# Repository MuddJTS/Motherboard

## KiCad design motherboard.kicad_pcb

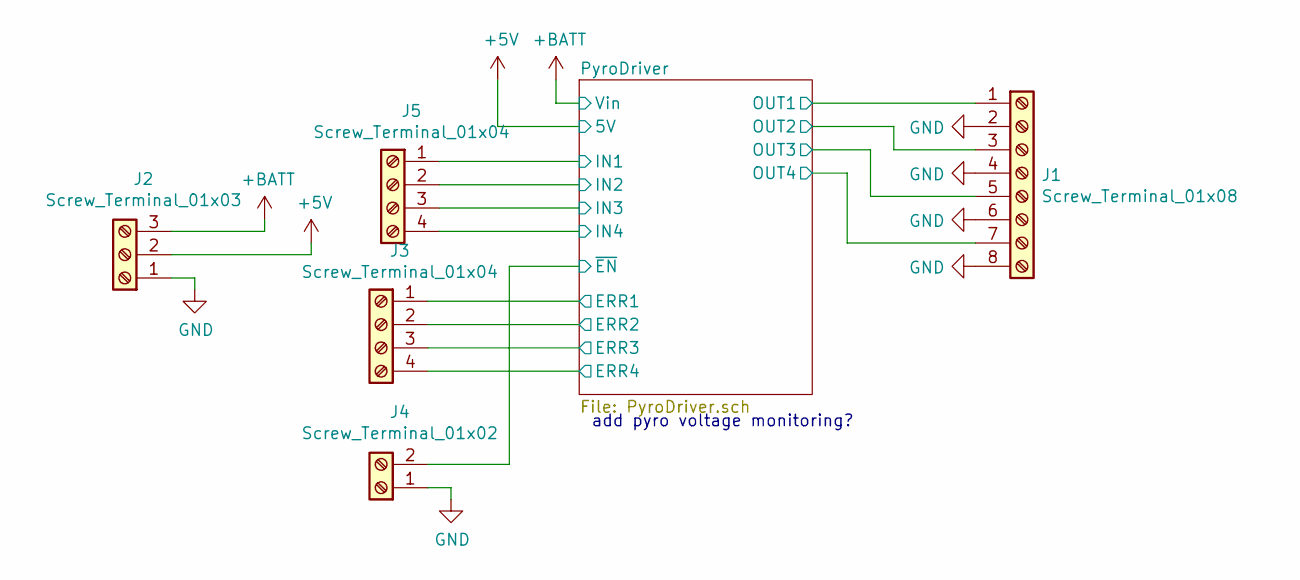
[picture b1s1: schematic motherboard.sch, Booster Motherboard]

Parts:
J1: Screw_Terminal_01x08; IDC-Header_2x04_Pitch2.54mm_Straight
J2: Screw_Terminal_01x03; TerminalBlock_bornier-3_P5.08mm
J3, J5: Screw_Terminal_01x04; TerminalBlock_bornier-4_P5.08mm
J4: Screw_Terminal_01x02; TerminalBlock_bornier-2_P5.08mm

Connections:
+5V: J2.2; also elsewhere on the board
+BATT: J2.3; also elsewhere on the board
/PyroDriver/ERR1: J3.1; also elsewhere on the board
/PyroDriver/ERR2: J3.2; also elsewhere on the board
/PyroDriver/ERR3: J3.3; also elsewhere on the board
/PyroDriver/ERR4: J3.4; also elsewhere on the board
/PyroDriver/IN1: J5.1; also elsewhere on the board
/PyroDriver/IN2: J5.2; also elsewhere on the board
/PyroDriver/IN3: J5.3; also elsewhere on the board
/PyroDriver/IN4: J5.4; also elsewhere on the board
/PyroDriver/OUT1: J1.1; also elsewhere on the board
/PyroDriver/OUT2: J1.3; also elsewhere on the board
/PyroDriver/OUT3: J1.5; also elsewhere on the board
/PyroDriver/OUT4: J1.7; also elsewhere on the board
/PyroDriver/~EN: J4.2; also elsewhere on the board
GND: J1.2, J1.4, J1.6, J1.8, J2.1, J4.1; also elsewhere on the board

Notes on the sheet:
add pyro voltage monitoring?

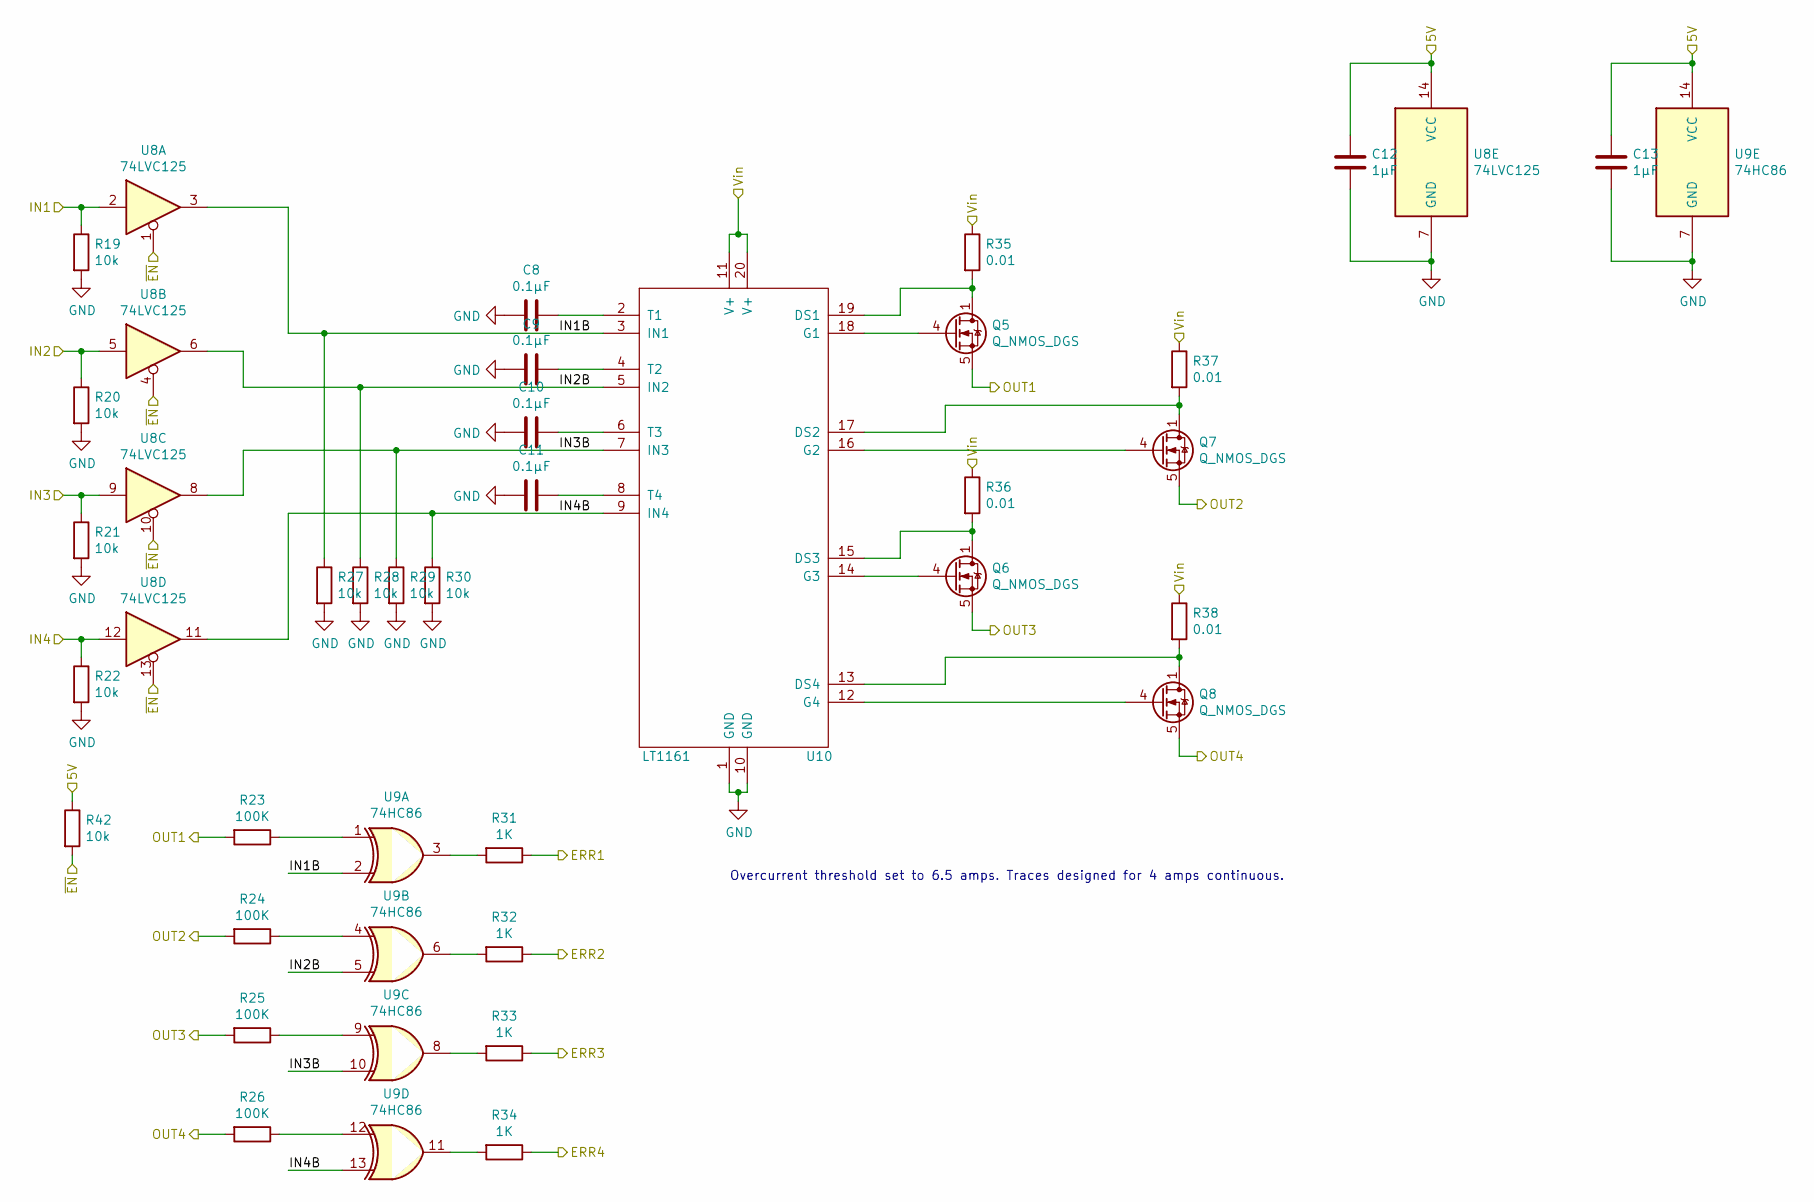
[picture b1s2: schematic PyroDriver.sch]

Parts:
C8, C9, C10, C11: 0.1µF; C_0603_1608Metric
C12, C13: 1µF; C_0603_1608Metric
Q5, Q6, Q7, Q8: Q_NMOS_DGS; PowerPAK_SO-8_Single
R19, R20, R21, R22, R27, R28, R29, R30, R42: 10k; R_0603_1608Metric
R23, R24, R25, R26: 100K; R_0603_1608Metric
R31, R32, R33, R34: 1K; R_0603_1608Metric
R35, R36, R37, R38: 0.01; R_0805_2012Metric
U8: 74LVC125; SOIC-14_3.9x8.7mm_Pitch1.27mm
U9: 74HC86; SOIC-14_3.9x8.7mm_Pitch1.27mm
U10: LT1161; Infineon_PG-DSO-20-32

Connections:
+5V: C12.1, C13.1, R42.1, U8.14 (VCC), U9.14 (VCC); also elsewhere on the board
+BATT: R35.1, R36.1, R37.1, R38.1, U10.11 (V+), U10.20 (V+); also elsewhere on the board
/PyroDriver/ERR1: R31.1; also elsewhere on the board
/PyroDriver/ERR2: R32.1; also elsewhere on the board
/PyroDriver/ERR3: R33.1; also elsewhere on the board
/PyroDriver/ERR4: R34.1; also elsewhere on the board
/PyroDriver/IN1: R19.1, U8.2; also elsewhere on the board
/PyroDriver/IN1B: R27.1, U8.3, U9.2, U10.3 (IN1)
/PyroDriver/IN2: R20.1, U8.5; also elsewhere on the board
/PyroDriver/IN2B: R28.1, U8.6, U9.5, U10.5 (IN2)
/PyroDriver/IN3: R21.1, U8.9; also elsewhere on the board
/PyroDriver/IN3B: R29.1, U8.8, U9.10, U10.7 (IN3)
/PyroDriver/IN4: R22.1, U8.12; also elsewhere on the board
/PyroDriver/IN4B: R30.1, U8.11, U9.13, U10.9 (IN4)
/PyroDriver/OUT1: Q5.5 (S), R23.2; also elsewhere on the board
/PyroDriver/OUT2: Q7.5 (S), R24.2; also elsewhere on the board
/PyroDriver/OUT3: Q6.5 (S), R25.2; also elsewhere on the board
/PyroDriver/OUT4: Q8.5 (S), R26.2; also elsewhere on the board
/PyroDriver/~EN: R42.2, U8.1, U8.4, U8.10, U8.13; also elsewhere on the board
GND: C8.2, C9.2, C10.2, C11.2, C12.2, C13.2, R19.2, R20.2, R21.2, R22.2, R27.2, R28.2, R29.2, R30.2, U8.7 (GND), U9.7 (GND), U10.1 (GND), U10.10 (GND); also elsewhere on the board
unnamed: C8.1, U10.2 (T1)
unnamed: C9.1, U10.4 (T2)
unnamed: C10.1, U10.6 (T3)
unnamed: C11.1, U10.8 (T4)
unnamed: Q5.1 (D), Q5.2, Q5.3, R35.2, U10.19 (DS1)
unnamed: Q5.4 (G), U10.18 (G1)
unnamed: Q6.1 (D), Q6.2, Q6.3, R36.2, U10.15 (DS3)
unnamed: Q6.4 (G), U10.14 (G3)
unnamed: Q7.1 (D), Q7.2, Q7.3, R37.2, U10.17 (DS2)
unnamed: Q7.4 (G), U10.16 (G2)
unnamed: Q8.1 (D), Q8.2, Q8.3, R38.2, U10.13 (DS4)
unnamed: Q8.4 (G), U10.12 (G4)
unnamed: R23.1, U9.1
unnamed: R24.1, U9.4
unnamed: R25.1, U9.9
unnamed: R26.1, U9.12
unnamed: R31.2, U9.3
unnamed: R32.2, U9.6
unnamed: R33.2, U9.8
unnamed: R34.2, U9.11

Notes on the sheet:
Overcurrent threshold set to 6.5 amps. Traces designed for 4 amps continuous.

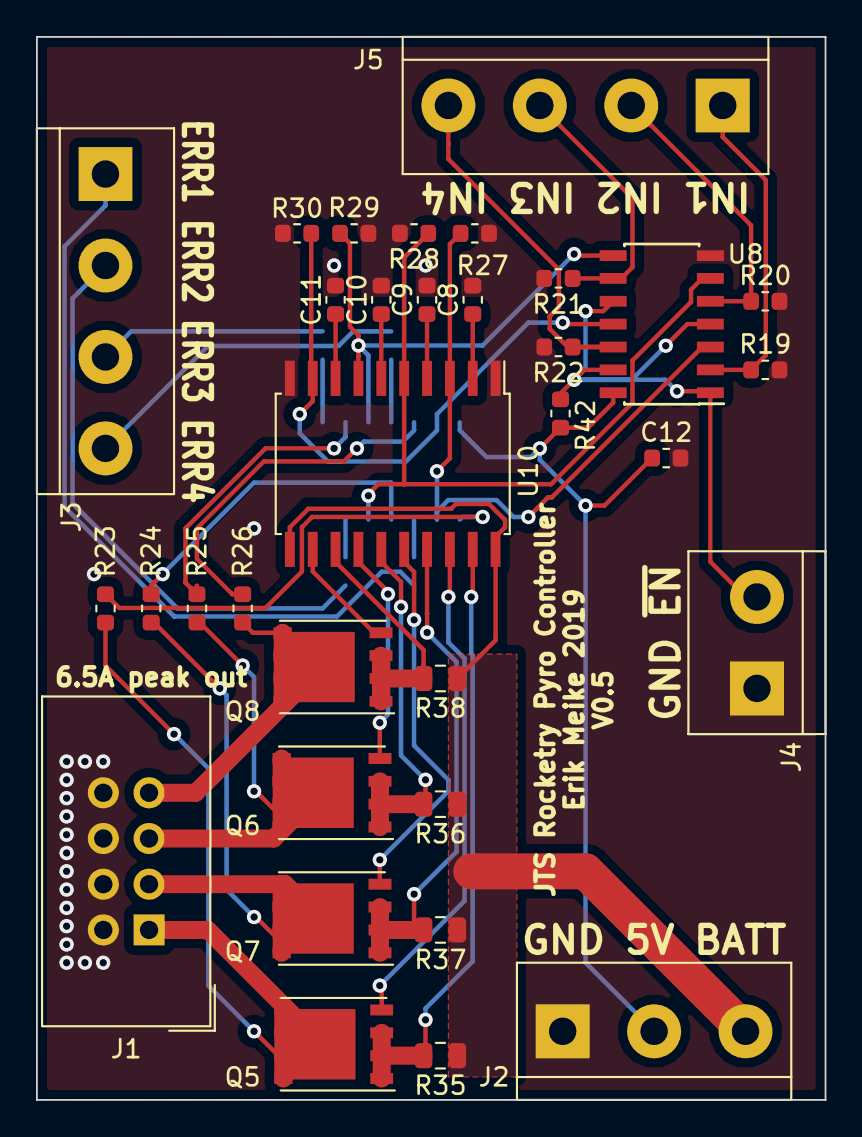
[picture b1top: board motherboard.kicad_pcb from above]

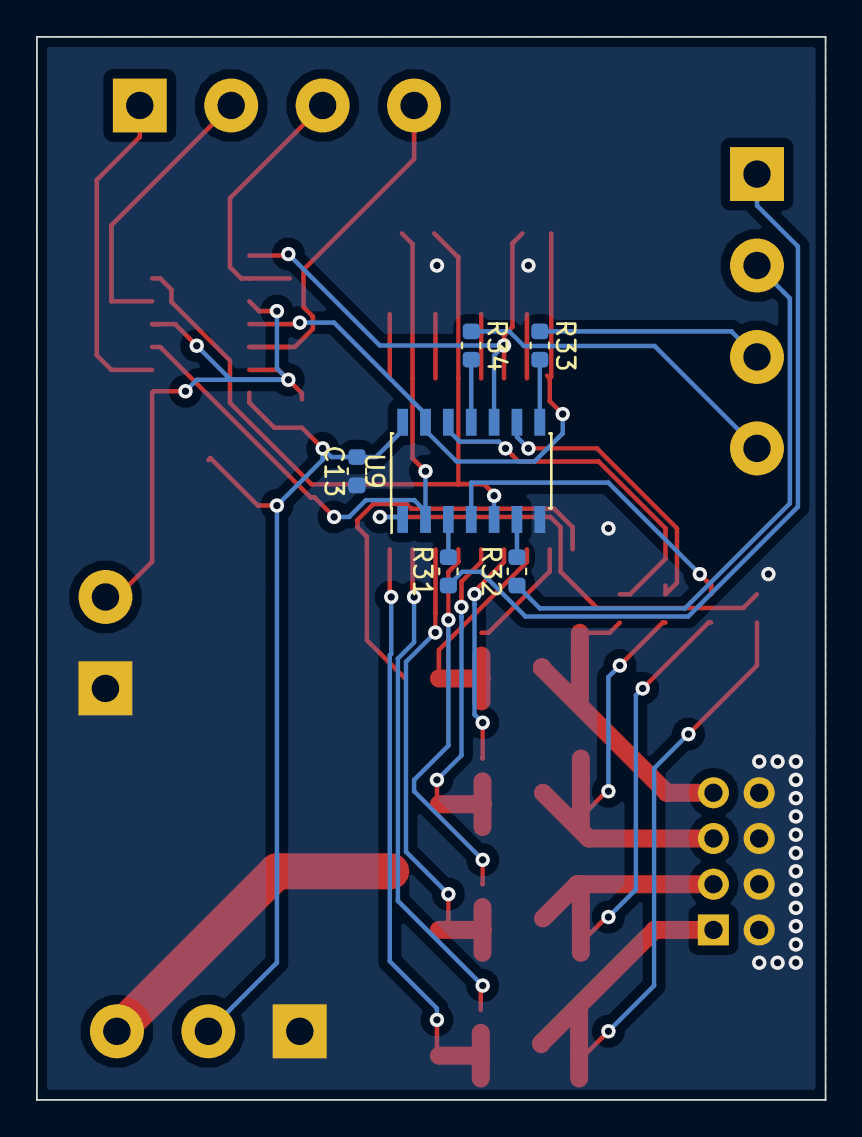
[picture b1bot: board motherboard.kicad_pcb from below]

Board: 4 copper layers, 43.8 x 59.1 mm, 39 parts (6 on the bottom side), 40 nets.

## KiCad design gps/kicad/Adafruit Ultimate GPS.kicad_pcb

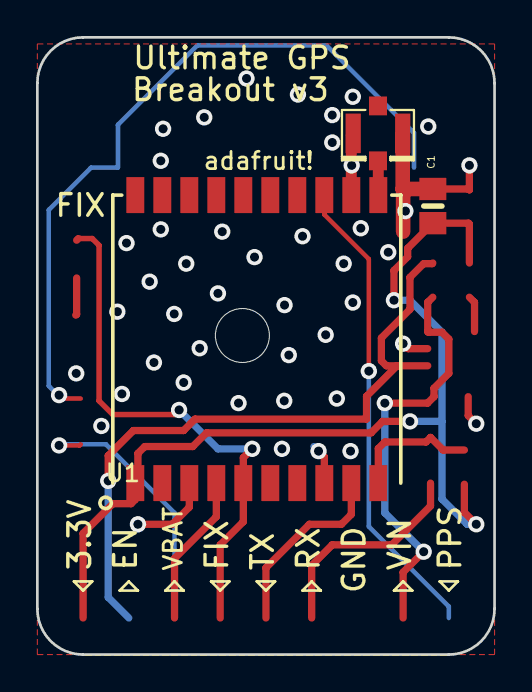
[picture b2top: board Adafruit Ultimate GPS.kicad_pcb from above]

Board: 2 copper layers, 25.4 x 34.3 mm, 3 parts (0 on the bottom side), 3 nets.

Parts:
C1: 0.1uF; 0805-NO
U1: FGPMMOPA6H
U$20: U.FL

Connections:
3.3V: C1.1, U1.P$1
GND: C1.2, U1.P$3, U1.P$8, U1.P$12, U1.P$19, U$20.P$1, U$20.P$2
unnamed: U1.P$11, U$20.P$3

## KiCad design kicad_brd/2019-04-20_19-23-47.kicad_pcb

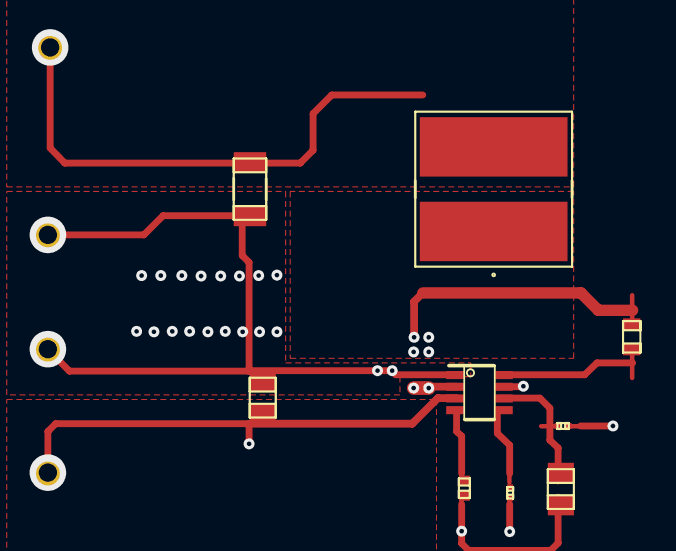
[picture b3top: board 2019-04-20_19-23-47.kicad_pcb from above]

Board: 10 copper layers, 13 parts (0 on the bottom side), 8 nets.

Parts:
Cbst: 0603
Cin: 0805
Cout: 1206
Css: 0201
GND, GND1: TP-1502
L1: VLP8040
Rfbb: 0201
Rfbt: 0805
Rpg: 0402
U1: DDF0008A_N
VIN: TP-1502
VOUT: TP-1502

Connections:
0: Cin.2, Cout.2, Css.2, GND.1, GND1.1, Rfbb.2, U1.1
2: Rfbb.1, Rfbt.2, U1.6
4: Cbst.1, L1.1, U1.2
6: Cout.1, L1.2, Rfbt.1, Rpg.1, VOUT.1
8: Cbst.2, U1.8
10: Rpg.2, U1.4
12: Css.1, U1.5
14: Cin.1, U1.3, U1.7, VIN.1

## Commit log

2019-04-21 added GPS schematic and layout
2019-04-21 added library
2019-04-21 Added TPS library
2019-04-21 Updated TI Automated Boost Converter
2019-04-21 added two components
2019-04-21 added TPS61175 Q1
2019-04-21 added power supply schematic and board files
2019-04-21 combined libraries
2019-04-28 created regulators, thermocouple, and radio
2019-04-30 new components
2019-04-30 start of pyro
2019-04-30 completed pyrodriver
2019-04-30 made LTC4412 footprint
2019-04-30 added 5V and schematic layout changes
2019-05-01 re-annotated and added 100G Accelerometer
2019-05-01 update gitignore
2019-05-01 swapped annotation error
2019-05-01 fixed naming
2019-05-01 created footprints and layout file
2019-05-02 starting layout
2019-05-05 board layed out ish
2019-05-05 add processor schematic file
2019-05-05 before netlist import with new footprints
2019-05-06 swapped 3d models and started routing
2019-11-12 more updates
